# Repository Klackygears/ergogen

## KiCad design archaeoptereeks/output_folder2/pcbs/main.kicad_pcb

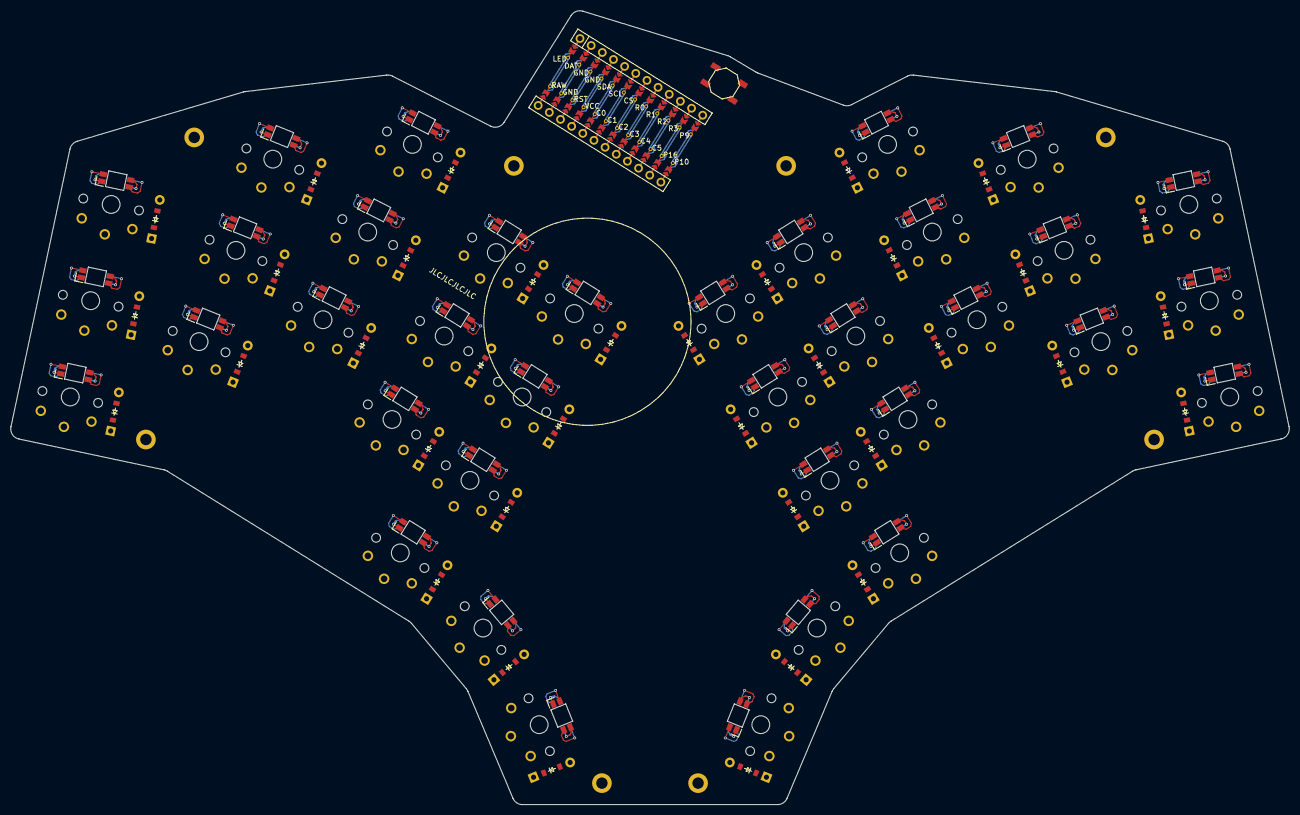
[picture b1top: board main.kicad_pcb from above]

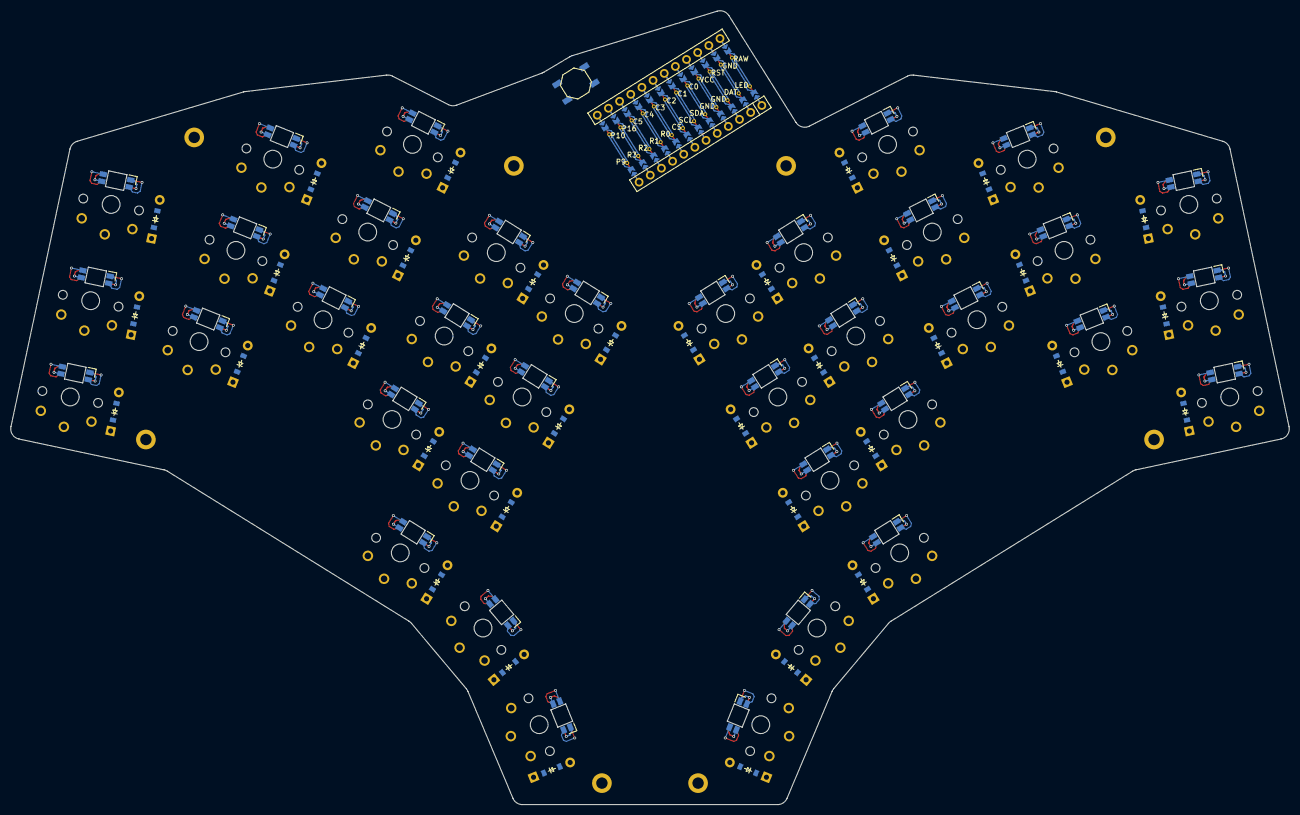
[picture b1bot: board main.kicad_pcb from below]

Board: 2 copper layers, 246.9 x 153.3 mm, 119 parts (36 on the bottom side), 89 nets.

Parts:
B1, B2: SW_TACT_ALPS_SKQGABE010
D1, D2, D3, D4, D5, D6, D7, D8, D9, D10, D11, D12, D13, D14, D15, D16, D17, D18, D19, D20, D21, D22, D23, D24, D25, D26, D27, D28, D29, D30, D31, D32, D33, D34, D35, D36: ComboDiode
H1, H2, H3, H4, H5, H6, H7, H8: mounting_hole
LED1, LED2, LED3, LED4, LED5, LED6, LED7, LED8, LED9, LED10, LED11, LED12, LED13, LED14, LED15, LED16, LED17, LED18, LED19, LED20, LED21, LED22, LED23, LED24, LED25, LED26, LED27, LED28, LED29, LED30, LED31, LED32, LED33, LED34, LED35, LED36: YS-SK6812MINI-E (per-key, reversible)
MCU1: nice_nano
S1, S2, S3, S4, S5, S6, S7, S8, S9, S10, S11, S12, S13, S14, S15, S16, S17, S18, S19, S20, S21, S22, S23, S24, S25, S26, S27, S28, S29, S30, S31, S32, S33, S34, S35, S36: PG1350

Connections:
C0: D2.1, D5.1, D8.1, D11.1, D14.1, D20.1, D23.1, D26.1, D29.1, D32.1, MCU1.5
C1: D1.1, D4.1, D7.1, D10.1, D13.1, D19.1, D22.1, D25.1, D28.1, D31.1, MCU1.6
C2: D16.1, D17.1, D18.1, D34.1, D35.1, D36.1, MCU1.7
C3: MCU1.8, S31.1, S32.1, S33.1
C4: MCU1.9, S28.1, S29.1, S30.1, S36.1
C5: MCU1.10, S25.1, S26.1, S27.1, S35.1
CS: MCU1.118, S7.1, S8.1, S9.1, S17.1
GND: B1.1, B2.1, LED1.3, LED2.3, LED3.3, LED4.3, LED5.3, LED6.3, LED7.3, LED8.3, LED9.3, LED10.3, LED11.3, LED12.3, LED13.3, LED14.3, LED15.3, LED16.3, LED17.3, LED18.3, LED19.3, LED20.3, LED21.3, LED22.3, LED23.3, LED24.3, LED25.3, LED26.3, LED27.3, LED28.3, LED29.3, LED30.3, LED31.3, LED32.3, LED33.3, LED34.3, LED35.3, LED36.3, MCU1.2, MCU1.121, MCU1.122
LED: LED3.4, MCU1.124
LED_2: LED2.4, LED3.2
LED_3: LED1.4, LED2.2
LED_4: LED1.2, LED4.4
LED_5: LED4.2, LED5.4
LED_6: LED5.2, LED6.4
LED_7: LED6.2, LED9.4
LED_8: LED8.4, LED9.2
LED_9: LED7.4, LED8.2
LED_10: LED7.2, LED10.4
LED_11: LED10.2, LED11.4
LED_12: LED11.2, LED12.4
LED_13: LED12.2, LED15.4
LED_14: LED14.4, LED15.2
LED_15: LED13.4, LED14.2
LED_16: LED13.2, LED16.4
LED_17: LED16.2, LED17.4
LED_18: LED17.2, LED18.4
LED_19: LED18.2, LED36.4
LED_20: LED35.4, LED36.2
LED_21: LED34.4, LED35.2
LED_22: LED31.4, LED34.2
LED_23: LED31.2, LED32.4
LED_24: LED32.2, LED33.4
LED_25: LED30.4, LED33.2
LED_26: LED29.4, LED30.2
LED_27: LED28.4, LED29.2
LED_28: LED25.4, LED28.2
LED_29: LED25.2, LED26.4
LED_30: LED26.2, LED27.4
LED_31: LED24.4, LED27.2
LED_32: LED23.4, LED24.2
LED_33: LED22.4, LED23.2
LED_34: LED19.4, LED22.2
LED_35: LED19.2, LED20.4
LED_36: LED20.2, LED21.4
P9: D3.1, D6.1, D9.1, D12.1, D15.1, D21.1, D24.1, D27.1, D30.1, D33.1, MCU1.113
P10: MCU1.12, S19.1, S20.1, S21.1
P16: MCU1.11, S22.1, S23.1, S24.1, S34.1
R0: MCU1.117, S4.1, S5.1, S6.1, S16.1
R1: MCU1.116, S1.1, S2.1, S3.1
R2: MCU1.115, S10.1, S11.1, S12.1, S18.1
R3: MCU1.114, S13.1, S14.1, S15.1
RST: B1.2, B2.2, MCU1.3
VCC: LED1.1, LED2.1, LED3.1, LED4.1, LED5.1, LED6.1, LED7.1, LED8.1, LED9.1, LED10.1, LED11.1, LED12.1, LED13.1, LED14.1, LED15.1, LED16.1, LED17.1, LED18.1, LED19.1, LED20.1, LED21.1, LED22.1, LED23.1, LED24.1, LED25.1, LED26.1, LED27.1, LED28.1, LED29.1, LED30.1, LED31.1, LED32.1, LED33.1, LED34.1, LED35.1, LED36.1, MCU1.4
far_thumb: D18.2, S18.2
home_thumb: D17.2, S17.2
index_bottom: D10.2, S10.2
index_home: D11.2, S11.2
index_top: D12.2, S12.2
inner_bottom: D13.2, S13.2
inner_home: D14.2, S14.2
inner_top: D15.2, S15.2
middle_bottom: D7.2, S7.2
middle_home: D8.2, S8.2
middle_top: D9.2, S9.2
mirror_far_thumb: D36.2, S36.2
mirror_home_thumb: D35.2, S35.2
mirror_index_bottom: D28.2, S28.2
mirror_index_home: D29.2, S29.2
mirror_index_top: D30.2, S30.2
mirror_inner_bottom: D31.2, S31.2
mirror_inner_home: D32.2, S32.2
mirror_inner_top: D33.2, S33.2
mirror_middle_bottom: D25.2, S25.2
mirror_middle_home: D26.2, S26.2
mirror_middle_top: D27.2, S27.2
mirror_near_thumb: D34.2, S34.2
mirror_pinky_bottom: D19.2, S19.2
mirror_pinky_home: D20.2, S20.2
mirror_pinky_top: D21.2, S21.2
mirror_ring_bottom: D22.2, S22.2
mirror_ring_home: D23.2, S23.2
mirror_ring_top: D24.2, S24.2
near_thumb: D16.2, S16.2
pinky_bottom: D1.2, S1.2
pinky_home: D2.2, S2.2
pinky_top: D3.2, S3.2
ring_bottom: D4.2, S4.2
ring_home: D5.2, S5.2
ring_top: D6.2, S6.2

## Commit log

2023-11-17 messing with ergogen
2023-11-17 basic outline ready
2023-11-19 messing around
2023-11-20 broken index.js?
2023-11-20 yeah, I broke it
2023-11-20 broke
2023-11-20 borked
2023-11-20 rotary footprint has issues. adding no silk rotary footprint bc silk not desired and same issues
2023-11-20 removing net and model reference from rotary_nosilk.js
2023-11-24 working on matrix layout and routing
2023-11-26 adding mounting holes and top plate
2023-11-26 removing mount hole silk
2023-11-27 adjusting traces for mount holes
2023-11-29 playing with ergogen and working on silk drawings
2023-11-30 more silk drawing
2023-11-30 adding f.silk to the board
2023-12-01 adding silks, reworking routing, top & bottom plates
2023-12-01 adding images of pcb
